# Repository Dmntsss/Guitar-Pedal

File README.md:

# Guitar-Pedal
This is the attempt to make a distortion guitar pedal from scratch using the model of the boss DS-1 distortion pedal as  an inspiration

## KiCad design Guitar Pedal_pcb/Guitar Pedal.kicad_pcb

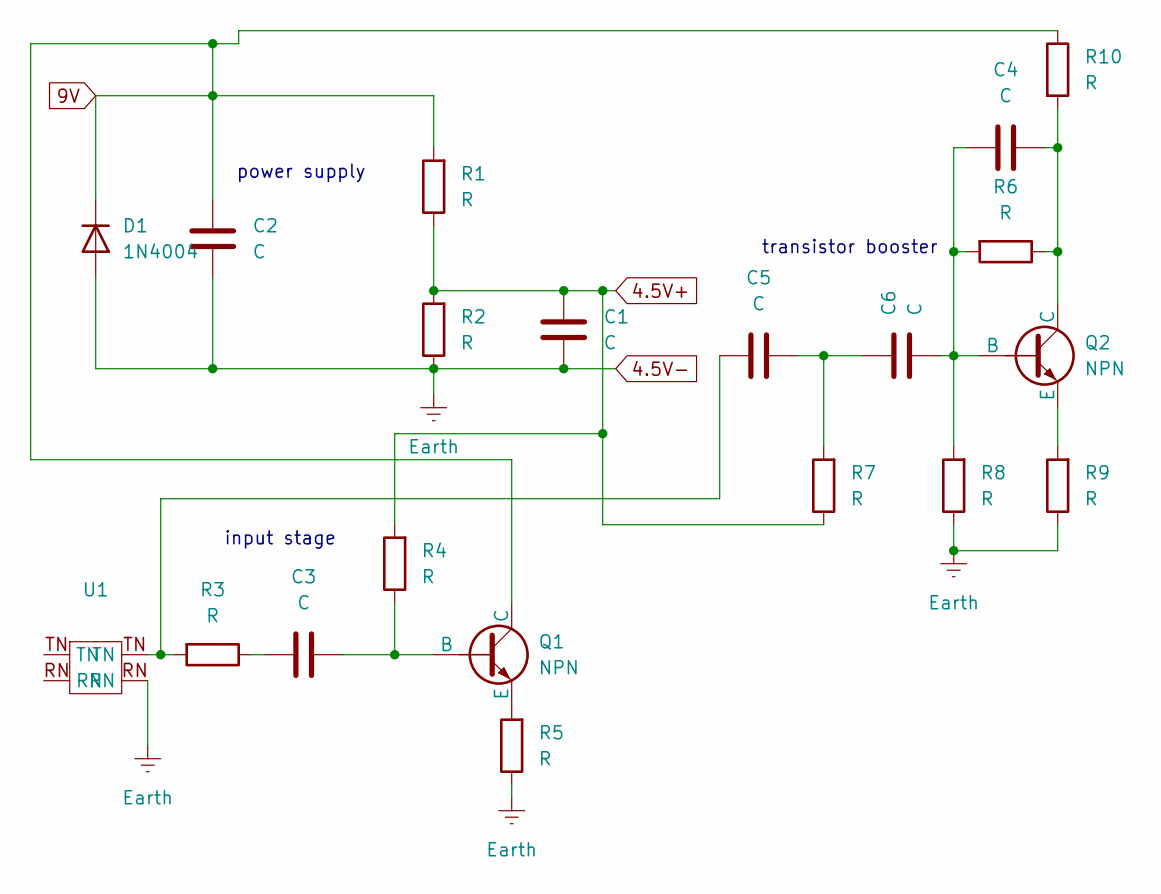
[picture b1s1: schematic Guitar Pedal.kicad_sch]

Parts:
C1, C2, C3, C4, C5, C6: C; CP_Radial_D10.0mm_P2.50mm
D1: 1N4004; D_DO-41_SOD81_P10.16mm_Horizontal
Q1, Q2: NPN; TO-92
R1, R2, R3, R4, R5, R6, R7, R8, R9, R10: R; R_Axial_DIN0204_L3.6mm_D1.6mm_P7.62mm_Horizontal
U1: Untitled

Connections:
4.5V+: C1.1, R1.1, R2.2, R4.2, R7.1
4.5V-: C1.2, C2.2, D1.2 (A), R2.1, R5.1, R8.1, R9.1, U1.RN
9V: C2.1, D1.1 (K), Q1.1 (C), R1.2, R10.1
unnamed: C3.1, R3.1
unnamed: C5.1, R3.2, U1.TN
unnamed: C5.2, C6.1, R7.2
unnamed: C3.2, Q1.2 (B), R4.1
unnamed: Q1.3 (E), R5.2
unnamed: C4.1, C6.2, Q2.2 (B), R6.2, R8.2
unnamed: C4.2, Q2.1 (C), R6.1, R10.2
unnamed: Q2.3 (E), R9.2

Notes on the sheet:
power supply
transistor booster
input stage

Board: 2 copper layers, 20 parts (0 on the bottom side), 11 nets, no tracks yet.

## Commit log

2026-04-13 power supply schematic
2026-04-19 initial theory push
2026-04-21 transistor booster μαζι με το μοντελο του transistor που θα βαλουμε (KSC1815)
2026-04-22 small tweak on the sourse Vpp
2026-05-03 amplification_stage with opamp lib
2026-06-07 unfinished kicad shematic and pcb
